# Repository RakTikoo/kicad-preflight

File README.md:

# KiCad Preflight

Check a KiCad project *before* you export Gerbers and order the board —
and check a BOM from any EDA tool before you order the parts.

Every maker knows the sinking feeling: the boards arrive and a footprint
is wrong, a part was never placed, or the one chip the design needs went
obsolete six months ago. KiCad Preflight reads a KiCad project (or a
standalone BOM CSV) and gives you one plain-English report — **PASS**,
**CAUTION**, or **BLOCK** — from deterministic checks: schematic ↔ PCB
agreement, BOM sanity, and offline part-risk flags. No LLM decides the
verdict: the same project always gets the same answer, and every finding
names the exact part and the exact values that disagree, so you can
verify it by hand in seconds.

Preflight is free and open source (MIT). There is no hosted tier and no
paid version — the whole tool lives in this repository.

## 30-second demo

```console
$ python3 -m preflight samples/broken
Preflight report for: LED Board (broken fixture)

Findings: 7 (5 BLOCK, 2 CAUTION, 0 NOTE)
  [BLOCK] SCH_PART_NOT_ON_PCB — led-board.kicad_sch · R3
      R3 (330R) is in the schematic but has no footprint on the PCB. ...
  [BLOCK] FOOTPRINT_MISMATCH — led-board.kicad_sch · D1
      1 part(s) (D1): the schematic asks for footprint
      'LED_SMD:LED_0805_2012Metric' but the PCB has
      'LED_SMD:LED_1206_3216Metric'. ...
  [BLOCK] BOM_QUANTITY_MISMATCH — bom.csv line 5
      BOM line 5 says quantity '3' but lists 2 reference(s) (D1, D2). ...
  [BLOCK] BOM_UNKNOWN_REFERENCE — bom.csv line 7
      The BOM lists C9, but there is no C9 in the schematic. ...
  [BLOCK] PART_OBSOLETE — bom.csv line 5 · LTST-C170KGKT
      LTST-C170KGKT (D1, D2) is marked 'obsolete' in the
      Preflight sample distributor dataset (snapshot 2026-11-09). ...
  [CAUTION] BOM_MISSING_MPN — bom.csv line 6
      BOM line 6 (SW1) has no manufacturer part number and no
      LCSC/JLCPCB part number. ...
  [CAUTION] PART_LOW_STOCK — bom.csv line 3 · RC0603FR-071KL
      ... shows only 8 in stock ... fewer than the 50-piece comfort line. ...

VERDICT: BLOCK
$ echo $?
2
$ python3 -m preflight samples/good     # the same board, fixed
VERDICT: PASS                           # exit 0, zero findings
```

(The samples are hand-authored fixtures — see "Test corpus". They are
only ever parsed, never opened in KiCad or fabricated.)

## KiCad-first, not KiCad-only

KiCad is the wedge, by design: it is the free, open tool whose users
feel these mistakes most, and its Plugin and Content Manager is a real
distribution channel. But the checks are not KiCad-only:

- The **KiCad parser** reads `.kicad_sch` / `.kicad_pcb` (KiCad 6, 7
  and 8 formats, hierarchical sheets included).
- The **BOM checks are tool-agnostic** — they live in their own module
  (`preflight/bomchecks.py`, fed by `preflight/bom.py`) and run on any
  BOM CSV. A BOM exported from Altium, Eagle/Fusion, EasyEDA or a fab
  house (JLCPCB style included) has the same classes of problems:

```console
$ python3 -m preflight production-bom.csv     # standalone BOM mode
```

- The planned **order-page browser extension** (JLCPCB/PCBWay
  checkout) is the later, any-tool front door. The full reasoning is
  in `EXTENSIONS_AND_GITHUB.md`.

## Two front doors, one engine

1. **This CLI (now)** — scriptable, testable without a GUI, runs in CI,
   works anywhere Python 3 runs.
2. **A KiCad in-app plugin (in development)** — one click inside
   KiCad at the moment before Gerber export, wrapping this same
   engine, distributed through KiCad's **Plugin and Content Manager
   (PCM)**. The package (identifier
   `com.github.RakTikoo.kicad-preflight`) lives in `pcm/`; it has run
   inside a real KiCad 8.0.9 PCB Editor (report dialog with live
   findings, probe 2026-11-10) — automatic discovery by a stock PCM
   install is the one check still pending, and the Limitations
   section below says exactly that.

## Install / usage

Pure Python 3 standard library (3.10+). No `pip install`, no
dependencies. KiCad itself is **not** required — see "Official checks".

```bash
python3 -m preflight <project-folder>                 # text report
python3 -m preflight <project-folder> --format md     # one-page Markdown
python3 -m preflight <project-folder> --format json   # machine-readable
python3 -m preflight <project-folder> --output report.md --format md
python3 -m preflight <bom.csv>                        # standalone BOM mode
python3 preflight.py <project-folder>                 # shim, same thing
```

The target can be a project folder or a single `.kicad_pro` /
`.kicad_sch` / `.kicad_pcb` file inside one. A BOM CSV in the folder is
auto-detected — candidates are tried in name order and the first whose
header actually parses as a BOM wins, so a pick-and-place CSV is never
mistaken for the BOM (or pass `--bom`).

Exit codes: `0` PASS · `1` CAUTION · `2` BLOCK · `3` usage error.
The CLI never prints a traceback; bad inputs exit 3 with a message.

## What it checks

The full rule list with severities is in `docs/RULES.md`. In short:

**Schematic ↔ PCB** (parsed from KiCad's S-expression files, KiCad 6
`fp_text` and KiCad 7/8 `property` styles alike): parts in the
schematic with no footprint on the PCB and vice versa, footprint
mismatches (aggregated per footprint pair), duplicate references,
two different parts sharing one reference, parts with no footprint /
no value / a placeholder MPN, unannotated symbols. Board furniture —
mounting holes marked `board_only`, silkscreen logos and labels with
generated references — is recognised as furniture, not flagged as
parts. Since v0.5 Preflight also extracts the schematic netlist
and checks pins and nets itself (ERC-lite + pin-level parity,
below); full DRC/ERC still belong to KiCad (below).

**BOM ↔ schematic** (KiCad, JLCPCB and generic header spellings):
references that don't exist, schematic parts missing from the BOM,
DNP / not-in-BOM parts that snuck into the BOM, duplicate references,
quantity cells that disagree with the designator list (`"R1,R2,R5"`
lists and `R1-R3` / `R1-3` ranges are expanded), missing or placeholder
MPNs (an LCSC/JLCPCB part number counts as identified), blank-reference
rows, BOM footprint/value disagreements with the schematic, and one
part number used for two different parts.

**Fabrication readiness** (v0.3): a missing board outline (BLOCK —
nothing to cut), copper zones with no fill stored, and measured board
values against the published standard-process minimums of JLCPCB and
PCBWay — track width, drill and via sizes, annular rings, plated slot
widths (CAUTION: below-standard means an engineering question or an
advanced process, not an automatic rejection). If a position/CPL file
sits in the folder, its designators are checked against the board
(assembly orders). Files written by KiCad 9/10 are detected from
their format stamps and flagged honestly: newer constructs
(variants, pad stacks, embedded files) are not fully parsed, so those
files never pass in silence.

**Geometry-lite** (v0.4): a conservative distance-checking subset —
not DRC. Exact pad/track/arc/via shapes are measured for
different-net clearance and copper-to-edge distance against the
board's own stated design rules (`.kicad_pro` clearances and
netclasses) or, when the board states none, the published fab
minimums; and the Edge.Cuts outline is chained to prove it closes.
What cannot be measured exactly is never approximated into a
finding: zones, custom/trapezoid pads and objects with no stated
net are excluded and listed in Coverage instead.

**Gerber package** (v0.4): point Preflight at the folder you are
about to upload to the fab and it checks the package itself —
top/bottom copper, masks, silkscreen, outline and drill file
present, no zero-byte or duplicated layers, a consistent layer
stack, one naming scheme (KiCad defaults, Protel extensions, or
generic names). Auto-detected for fab-output folders, or forced
with `--gerber`. File-level only: Gerber contents are never parsed.

**Netlist: ERC-lite + schematic↔PCB parity** (v0.5): the schematic
netlist is extracted natively (pin connection points computed from
library definitions and symbol transforms, nets built from wires,
junctions, labels and sheet pins, KiCad label/hierarchy semantics).
On top of it: unconnected pins with no no-connect marker, power
nets no power-output pin drives (KiCad's documented power-pin
test), output conflicts per KiCad's pin-conflict matrix, dangling
labels, and pin-level parity between the schematic netlist and
the PCB's pads — membership differences, nets present on one side
only, and renames. What cannot be resolved (missing library
definitions, unmodelled pad shapes, bus-only pins) abstains and is
counted in Coverage, never guessed.

**v0.6 — KiCad bridge, project settings, zones, online parts**:
when kicad-cli is installed, its DRC run now also surfaces
unconnected items and KiCad's own schematic-parity conflicts, and
the project's `.kicad_pro` ERC/DRC severities and exclusions are
read and honoured by BOTH the official-checks layer and the
matching native checks (waivers counted in Coverage). Geometry-lite
measures stored filled zone polygons (with a chord-certainty
tolerance proven against KiCad DRC itself). Parity membership now
covers trapezoid and modelled custom pads, and ERC-lite covers the
full set of ERROR cells in KiCad's documented pin-conflict matrix.
An opt-in `--online` mode (API keys from environment variables
only) checks live lifecycle/stock/lead time and price at DigiKey
or Mouser, superseding the sample dataset per part, plus a
semantic value↔part-number check for passives; without the flag
the tool makes zero network calls and output is unchanged. 88
rules in total; the full list is `docs/RULES.md`.

**Part risk (offline)**: obsolete/EOL, out-of-stock, low stock, long
lead time, single-source, not-recommended-for-new-designs — per BOM
MPN against the bundled dataset (see the honesty note). Numbers in a
user dataset may be strings or floats, as real exports produce; they
are coerced, not ignored.

## Coverage: a PASS only covers what was checked

Every report ends with a Coverage section: files parsed (all sheets of
a hierarchical design), parts and footprints counted, board furniture
excluded, BOM rows, MPNs checked, parse errors, and the kicad-cli
status. If something that exists could not be checked — an unloaded
extra project file, a failed kicad-cli run, a missing BOM — the report
carries a `SCAN_INCOMPLETE`, `BOM_MISSING` or stronger finding, so the
verdict reflects it. There are no silent skips.

## Official checks (kicad-cli)

If KiCad's `kicad-cli` is on your PATH, Preflight also runs the
official **DRC** (PCB) and **ERC** (schematic) and folds their
violations in (error → BLOCK, warning → CAUTION; a failed run's output
is never trusted, and user-excluded/unknown severities are counted in
Coverage, not silently mapped). If kicad-cli is absent, those checks
are skipped **and the report says so**. The built-in text checks work
either way.

## Budgets and untrusted input

Project folders are untrusted input, so scanning is budgeted: files
must be regular files (a FIFO will not hang the tool) and ≤ 64 MB;
BOMs and position files ≤ 20,000 rows and ≤ 1M characters per field;
reports cap at 2,000 findings with an explicit truncation note. Report output is
sanitised — crafted part values cannot forge a verdict line or break
the Markdown table. Files are decoded as strict UTF-8; corrupt bytes
are a parse error, never silently rewritten.

## An honest note on part data

The part-risk layer ships with a small **sample distributor dataset**
(`preflight/data/parts.json`, snapshot 2026-11-09) so it works offline
with no API keys. Its statuses and stock numbers are **illustrative,
not live distributor data** — every part-risk finding cites the dataset
and snapshot date, and an MPN absent from the dataset is reported as
"could not check", never guessed at. Supply your own snapshot with
`--dataset` (shape-validated; a bad dataset is a usage error, exit 3).

## Test corpus

- `samples/` — hand-authored fixtures in real KiCad formats:
  `good/` (PASS, zero findings), `kicad6/` (the same board in KiCad 6
  file format; PASS), `v9/` (the good board re-stamped as KiCad 9;
  CAUTION with exactly the two honest version warnings), `broken/`
  (seven deliberate, hand-verifiable errors; BLOCK with exactly the
  seven documented findings), and the v0.4 fixtures: `geo-ok/`
  (pads exactly at the stated clearance; geometry silent),
  `geo-violation/` (clearance + copper-to-edge findings),
  `geo-open/` (an unclosed outline; BLOCK), `gerber-good/`
  (a complete fab package; PASS), `gerber-incomplete/` and
  `gerber-inner-broken/` (package caution/BLOCK sets).
- `corpus/` — **real open-source boards** (Upsy Desky, the ESP32 Rust
  board, Piantor) with sources, commits and licences recorded in
  `corpus/SOURCES.md`, plus a labelled broken corpus built by mutating
  copies (`corpus/build_broken.py`). The corpus is downloaded
  separately; `run_corpus_tests.py` skips cleanly without it.

```bash
python3 run_tests.py           # samples
python3 run_corpus_tests.py    # open-source corpus + mutations
python3 run_edge_tests.py      # hostile inputs (from the adversarial review)
```

## How this version was reviewed

v0.1 was put through an independent multi-agent adversarial review —
a red team (hostile inputs), a false-positive tester (clean real
boards), and a code/security auditor — and failed it instructively
(100% of its BLOCKs on clean boards were false alarms; 7 crashes and
a FIFO hang on hostile inputs). v0.2 is the fix round: every reviewer
finding is either fixed or documented as an accepted gap, and the
reviewers' own test sets are the regression suites above. The full
record, with before/after numbers, is kept with the project.
v0.3 (the coverage wave) went through the same three-reviewer
discipline for its new rules; `docs/COVERAGE.md` maps every pre-order
failure class we know of against this tool and the open-source
alternatives, gaps included.
v0.4 (geometry-lite + Gerber package checks) went through the same
discipline again: the three reviewers produced 21 red-team cases, a
clean-corpus verdict that failed on exactly two real bugs, and a
worst-case runtime audit that refuted the first build's budget
claims on crafted inputs. Every confirmed finding was fixed or
documented as an accepted limit; the reviewers' inputs are now
regression tests in the edge suite (§17).
v0.5 (netlist / ERC-lite / parity) and v0.6 (KiCad bridge, project
settings, zones, online parts) went through the same discipline —
for v0.6 including a dedicated key-handling/network security pass
over the online mode — with every wave's before/after numbers kept
in the project's review record.

## Known limits

- **Live distributor data is opt-in** — by default part risk is
  only as real as the dataset supplied (see above); `--online`
  checks live data at DigiKey/Mouser with API keys taken from
  environment variables only.
- **kicad-cli is optional** — without it there is no official DRC/ERC;
  Coverage always says which mode you got.
- **Geometry is a subset, honestly labelled** — geometry-lite
  measures clearances and copper-to-edge for pads/tracks/arcs/vias
  with exact shapes, filled zone polygons (with a chord-certainty
  tolerance), and proves outline closure; it does not check
  custom/trapezoid pad shapes, mask/silk/courtyard geometry,
  holes, or connectivity. Full spatial DRC remains kicad-cli's
  job (above), and `docs/COVERAGE.md` maps exactly which failure
  classes the subset leaves open. Gerber package checks are
  file-level only — a zipped package must be extracted first, and
  Gerber/drill contents are never parsed.
- **One project per folder** — hierarchical sheets of one project are
  followed; a second project sharing a folder is reported via
  `SCAN_INCOMPLETE`, not merged.
- **Legacy formats** — KiCad ≤5 `.sch` files are reported as
  unsupported, not silently misread.
- **Plugin: runs inside KiCad; PCM discovery check pending** — the
  `pcm/` package has run inside a real KiCad 8.0.9 PCB Editor: the
  report dialog produced live findings on a real board and plugin
  registration executes in-app (probe run on a VM under a virtual
  display, 2026-11-10). What has not been verified yet is automatic
  discovery by a stock desktop install — installing the PCM zip via
  KiCad's Plugin and Content Manager and confirming the menu entry
  appears. Status detail in `pcm/README.md`.

## Licence

MIT — see `LICENSE`. Copyright (c) 2026 RakTikoo.

---

**More from this workshop:** [SkillScan](https://github.com/RakTikoo/skillscan) · [Expiry Radar](https://github.com/RakTikoo/expiry-radar) · [CI Command Truth](https://github.com/RakTikoo/ci-command-truth) · [PhantomDep PR Gate](https://github.com/RakTikoo/phantomdep-pr-gate) · [Stranger Suite](https://github.com/RakTikoo/stranger-suite) · [Living Contract Diff](https://github.com/RakTikoo/living-contract-diff) · [Handoff Reconciler](https://github.com/RakTikoo/handoff-reconciler)

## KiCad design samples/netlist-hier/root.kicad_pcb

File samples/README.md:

# Sample projects

These are **hand-authored fixture projects**, written as text in the KiCad 8
S-expression formats (`.kicad_sch` / `.kicad_pcb`) with the same structure
KiCad itself writes — placed symbols with Reference/Value/Footprint
properties, footprint instances with pads, a `.kicad_pro`, and a KiCad-style
BOM CSV. They are *structurally real, graphically minimal*: the electrical
content (pins, nets, connectivity) is illustrative, not a board you should
fabricate. They exist so Preflight's checks can be tested end-to-end with
hand-verifiable expectations, the same discipline as SkillScan's sample
skills. Nothing here is executed; the files are only parsed.

## `easyeda-pro/` — synthetic standalone Pro BOMs

Comma-separated Pro-style header fixtures with known good and missing-part-number
outcomes; see [the fixture notes](easyeda-pro/README.md) for exact findings,
supplier mapping and the first-party format reference. The focused tests also
cover the documented tab-separated Pro header set. No real board/export data.

## `good/` — expected PASS (exit 0, zero findings)

A tiny battery LED board: J1 (battery connector), R1 (330R), D1/D2 (red
LEDs), SW1 (slide switch). Schematic, PCB, and BOM agree exactly, and every
BOM part is a healthy entry in the sample distributor dataset
(active, well stocked, multi-source, short lead).

## `kicad6/` — expected PASS (exit 0, zero findings)

The same tiny board written in the KiCad 6 file format: PCB footprints
carry `fp_text` references instead of `property` nodes, and schematic
symbols use `property` nodes without per-instance `instances` blocks.
Added after the adversarial review showed v0.1 could not read KiCad 6
boards at all (it flagged every part on them as missing).

## `broken/` — expected BLOCK (exit 2, exactly 7 findings)

The same style of board with seven deliberate, hand-verifiable errors:

| # | Planted error | Expected rule | Severity |
| --- | --- | --- | --- |
| 1 | R3 is in the schematic (and BOM) but has no footprint on the PCB | `SCH_PART_NOT_ON_PCB` | BLOCK |
| 2 | D1's schematic footprint is `LED_0805_2012Metric` but the PCB has `LED_1206_3216Metric` | `FOOTPRINT_MISMATCH` | BLOCK |
| 3 | The BOM lists C9, which does not exist in the schematic | `BOM_UNKNOWN_REFERENCE` | BLOCK |
| 4 | The D1,D2 BOM row says quantity 3 but lists 2 references | `BOM_QUANTITY_MISMATCH` | BLOCK |
| 5 | The LED's MPN (`LTST-C170KGKT`) is obsolete in the sample dataset | `PART_OBSOLETE` | BLOCK |
| 6 | SW1's BOM row has a blank MPN | `BOM_MISSING_MPN` | CAUTION |
| 7 | R1's MPN (`RC0603FR-071KL`) has only 8 in stock in the sample dataset | `PART_LOW_STOCK` | CAUTION |

If `run_tests.py` reports anything else for this folder, either the fixture
or the checker changed — that is what the test is for.

## `v9/` — expected CAUTION (exit 1, exactly 2 findings)

The `good/` board with its file-format stamps changed to KiCad 9
(schematic format 20250114, board format 20241229, generator_version
"9.0"). The design itself is unchanged and healthy; the two expected
findings are both `KICAD_VERSION_UNTESTED`, one per file — v0.3's
honest handling of KiCad 9/10 files, whose newer constructs (embedded
files, tables, pad stacks, design variants) the parser does not fully
understand. A silent PASS here would be a lie; a BLOCK would be one
too.

## `geo-ok/` — v0.4 geometry-lite: silence expected from the geometry rules

A PCB-only fixture (other layers' findings are not asserted): two
1×1 mm pads of different nets exactly 0.200 mm apart — the clearance
the fixture's own `.kicad_pro` states — a closed rectangular
outline, and one lone Edge.Cuts line (a routed slot). No
GEOMETRY_* finding and no BOARD_OUTLINE_OPEN may fire.

## `geo-violation/` — v0.4: GEOMETRY_CLEARANCE_BELOW_MIN + GEOMETRY_COPPER_TO_EDGE

Same board with the pads 0.05 mm apart, plus a third pad 0.10 mm
from the west edge (below the 0.20 mm published minimum the board
falls back to, stating no edge clearance of its own).

## `geo-open/` — v0.4: BOARD_OUTLINE_OPEN (BLOCK)

The geo-ok board with the west side of the outline deleted: three
chained lines whose endpoints do not pair up.

## `gerber-good/` — v0.4 package mode: PASS, zero findings

A complete KiCad-style fabrication package (top/bottom copper,
masks, silkscreens, outline, drill file, job file) with dummy
one-line contents — package checks are file-level, so contents are
never read. Auto-detected as a package (no KiCad files present).

## `gerber-incomplete/` — v0.4: exactly 4 CAUTIONs

Top copper, outline and drill present; the top mask file is
zero-byte (GERBER_EMPTY_FILE), and bottom copper, bottom mask and
silkscreen are absent (GERBER_BOTTOM_COPPER_MISSING,
GERBER_MASK_MISSING, GERBER_SILKSCREEN_MISSING).

## `gerber-inner-broken/` — v0.4: BLOCK

Protel-style package with inner copper (.g1/.g2) but no bottom
copper and no outline: GERBER_INNER_WITHOUT_BOTTOM +
GERBER_OUTLINE_MISSING (BLOCKs) plus drill/mask/silkscreen
cautions.

## `netlist-clean/` — v0.5 netlist: PASS, zero findings

A small matched schematic/PCB pair: connector → regulator → load,
GND power symbols plus a PWR_FLAG, local labels, and PCB pads whose
net membership matches the schematic exactly. Exercises ERC-lite
and parity silence on a healthy design.

## `netlist-hier/` — v0.5 netlist: PASS, zero findings

A root sheet with one sub-sheet: a sheet pin bound to a
hierarchical label inside, a global label crossing both sheets, a
power symbol in the sub-sheet, and PCB nets named the way KiCad
writes them (`/Sub/FEED`, `GND`, `SENSE_G`). Proves the hierarchy
plumbing end to end.

## `netlist-broken/` — v0.5 netlist: BLOCK, each fault exactly once

Planted faults: two drivers shorted on VOUT
(ERC_OUTPUT_CONFLICT), a power net with no power-output driver
(ERC_POWER_NOT_DRIVEN), one unconnected pin (ERC_UNCONNECTED_PIN;
a second pin carries a no-connect marker and stays silent), one
pad moved to a different net on the PCB
(PARITY_NET_MEMBERSHIP on both affected nets), one schematic-only
net (PARITY_NET_SCH_ONLY), and one renamed net with identical
membership (PARITY_NET_RENAMED, NOTE). One unrelated
PART_NOT_IN_SAMPLE_DATA NOTE comes from the sample parts dataset.

## `real/` — optional, not asserted

If real open-source KiCad projects were fetched during development, they
live here with their source and licence noted. They are smoke tests only
(the CLI must produce a report and a defined exit code); their findings are
third-party projects' real state and are **not** hand-verified, so
`run_tests.py` does not assert their verdicts.

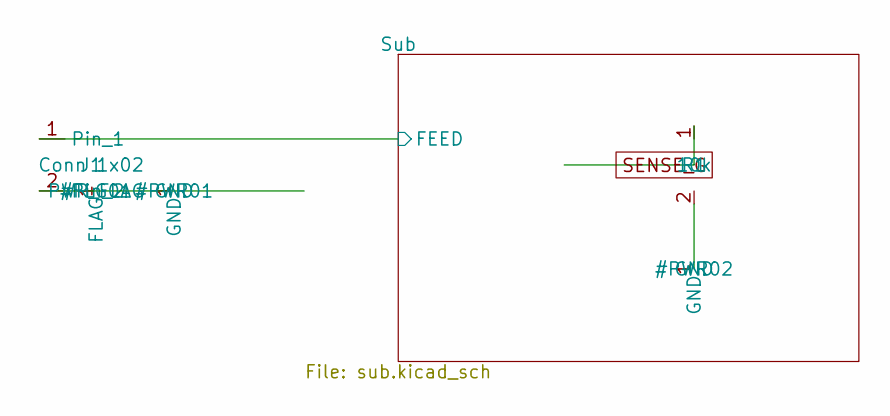
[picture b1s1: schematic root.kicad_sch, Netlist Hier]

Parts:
J1: Conn 1x02; JST_PH_B2B-PH-K_1x02_P2.00mm_Vertical
R1: 10k; R_0805_2012Metric

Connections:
/Sub/FEED: J1.1; also elsewhere on the board
GND: J1.2, R1.2; also elsewhere on the board
SENSE_G: R1.1; also elsewhere on the board

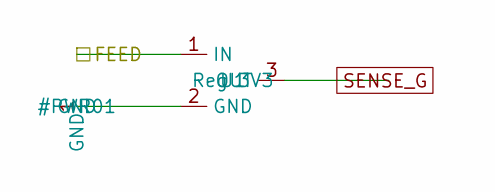
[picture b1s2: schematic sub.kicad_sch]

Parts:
U1: Reg 3V3; SOT-23

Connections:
/Sub/FEED: U1.1 (IN); also elsewhere on the board
GND: U1.2 (GND); also elsewhere on the board
SENSE_G: U1.3 (OUT); also elsewhere on the board

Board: 2 copper layers, 3 parts (0 on the bottom side), 3 nets, no tracks yet.

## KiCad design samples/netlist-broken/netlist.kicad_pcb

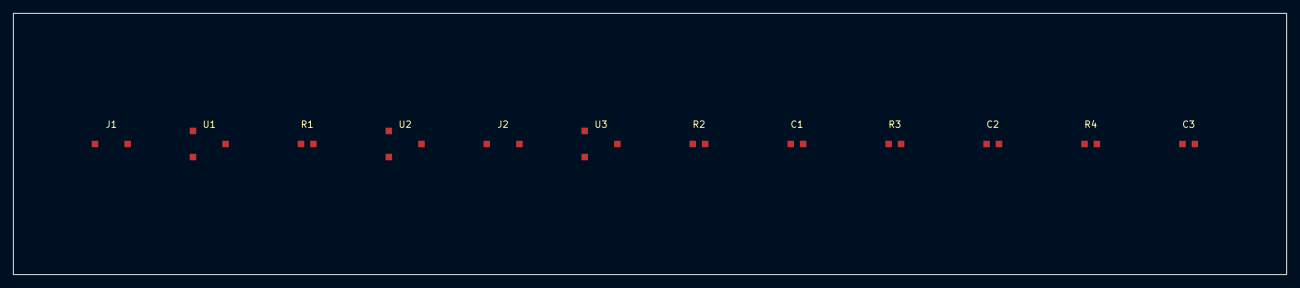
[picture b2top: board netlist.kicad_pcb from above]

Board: 2 copper layers, 195.0 x 40.0 mm, 12 parts (0 on the bottom side), 5 nets, no tracks yet.

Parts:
C1, C2, C3: 100n; C_0805_2012Metric
J1, J2: Conn 1x02; JST_PH_B2B-PH-K_1x02_P2.00mm_Vertical
R1, R2, R3, R4: 10k; R_0805_2012Metric
U1: Reg 3V3; SOT-23
U2: Driver; SOT-23
U3: Sensor; SOT-23

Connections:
CLK_OUT: C3.1, R4.1
GND: C1.1, C2.2, C3.2, J1.2, J2.2, R3.2, R4.2, U1.2, U2.2, U3.2
VBAT_IN: J2.1, U3.1
VIN: J1.1, U1.1, U2.1
VOUT: R1.1, R1.2, R2.1, U1.3, U2.3

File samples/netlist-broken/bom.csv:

Reference,Quantity,Value,Footprint,MPN
J1,1,Conn 1x02,Connector_JST:JST_PH_B2B-PH-K_1x02_P2.00mm_Vertical,B2B-PH-K-S
U1,1,Reg 3V3,Package_TO_SOT_SMD:SOT-23,LTST-C170KRKT
R1,1,10k,Resistor_SMD:R_0805_2012Metric,RC0805FR-07330RL
U2,1,Driver,Package_TO_SOT_SMD:SOT-23,JS102011SAQN
J2,1,Conn 1x02,Connector_JST:JST_PH_B2B-PH-K_1x02_P2.00mm_Vertical,B2B-PH-K-S
U3,1,Sensor,Package_TO_SOT_SMD:SOT-23,SENSOR-IC-001
R2,1,10k,Resistor_SMD:R_0805_2012Metric,RC0805FR-07330RL
C1,1,100n,Capacitor_SMD:C_0805_2012Metric,CL05B104KO5NNNC
R3,1,10k,Resistor_SMD:R_0805_2012Metric,RC0805FR-07330RL
C2,1,100n,Capacitor_SMD:C_0805_2012Metric,CL05B104KO5NNNC
R4,1,10k,Resistor_SMD:R_0805_2012Metric,RC0805FR-07330RL
C3,1,100n,Capacitor_SMD:C_0805_2012Metric,CL05B104KO5NNNC

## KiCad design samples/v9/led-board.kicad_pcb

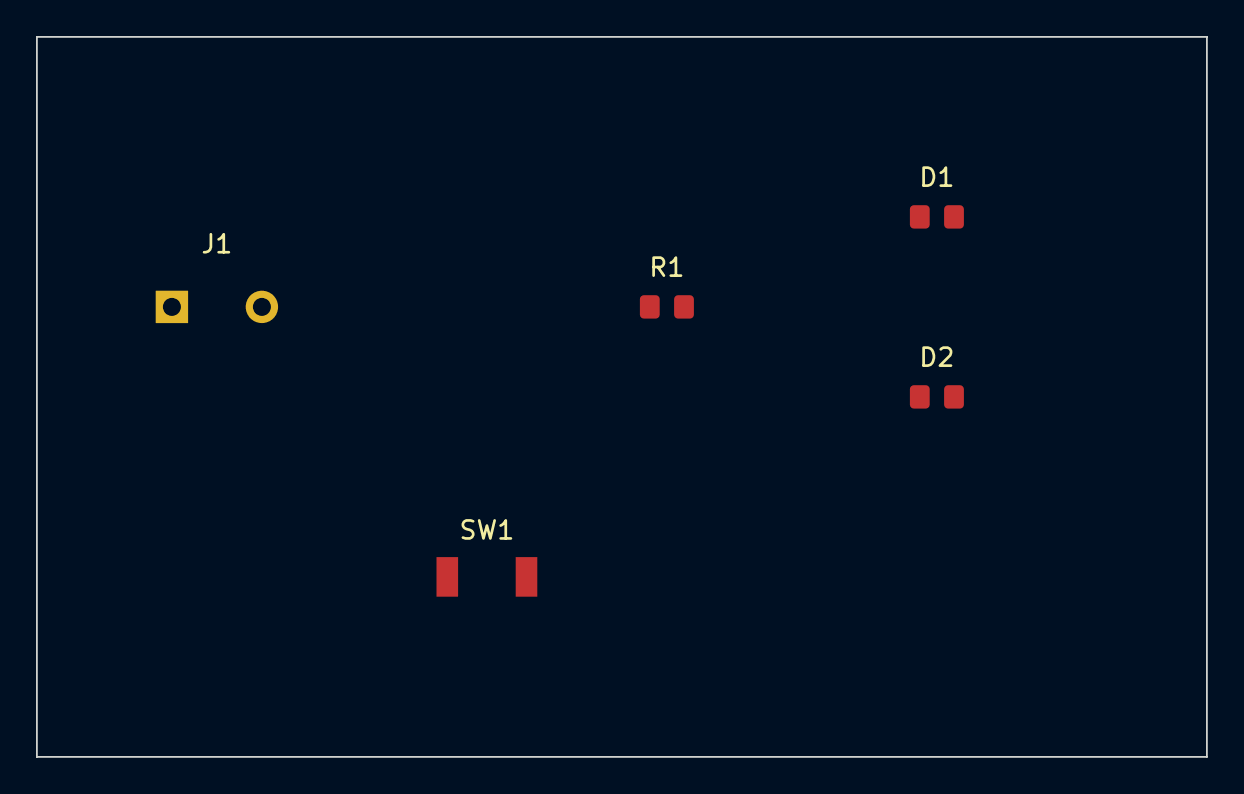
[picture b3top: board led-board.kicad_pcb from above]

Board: 2 copper layers, 65.0 x 40.0 mm, 5 parts (0 on the bottom side), 2 nets, no tracks yet.

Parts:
D1, D2: LED Red; LED_0805_2012Metric
J1: Battery; JST_PH_B2B-PH-K_1x02_P2.00mm_Vertical
R1: 330R; R_0805_2012Metric
SW1: SW Slide; SW_SPST_CK_JS102011SAQN

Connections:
GND: D1.1, D2.1, J1.2, R1.2, SW1.2
VBAT: D1.2, D2.2, J1.1, R1.1, SW1.1

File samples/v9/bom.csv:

Reference,Quantity,Value,Footprint,MPN,Manufacturer,Description
J1,1,Battery,Connector_JST:JST_PH_B2B-PH-K_1x02_P2.00mm_Vertical,B2B-PH-K-S,JST,Battery connector PH 2P vertical
R1,1,330R,Resistor_SMD:R_0805_2012Metric,RC0805FR-07330RL,Yageo,Chip resistor 330 ohm 0805
"D1,D2",2,LED Red,LED_SMD:LED_0805_2012Metric,LTST-C170KRKT,Lite-On,LED red 0805
SW1,1,SW Slide,Switch_SMD:SW_SPST_CK_JS102011SAQN,JS102011SAQN,C&K,Slide switch SPST SMD
